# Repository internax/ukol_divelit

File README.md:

# SPI FLASH programátor
Tento repozitář obsahuje souboru k návrhu SPI Flash programátoru.

## Struktura
- Výrobní soubory jsou v adresáři: programator_spi/production/programator_spi.zip
- Schéma je dostupné v adresáři: programator_spi/schema_pdf/programator_spi.pdf
# Návrhová rozhodnutí

## Patice pro DIP8

Původní záměr byl použít ZIF socket, ten se však pro pDIP8 pouzdro prakticky nevyrábí. Zvolil jsem proto přesnou patici z doporučených komponent. Klíčovými kritérii byl nízký odpor kontaktů a zlaté pokovení pinů. Životnost patice je dle dokumentace přibližně 500 cyklů, což by pro daný účel mělo být dostatečné. Pokud by se požadavky na počet cyklů zvýšily, bylo by nutné přejít na ZIF patici většího formátu.

## USB rozhraní

Nejprve jsem navrhl USB rozhraní. Použil jsem ESD ochranu z doporučených komponent. Zvažoval jsem ještě ECMF02-2AMX6, která nabízí common mode ochranu a je použita například v referenčním designu MB1801.

Dále jsem přidal proudovou ochranu — polyfuse. Maximální proud jsem stanovil takto: flash paměť odebírá při zápisu až 30 mA, MCU pak dle datasheetu až 150 mA. Zvolil jsem proto polyfuse 200 mA, která poskytuje rozumnou rezervu; v případě potřeby ji lze snadno vyměnit.

Dle specifikace jsem na linku D+ přidal pull-up rezistor 1k5Ω.

## MCU

S STM32 jsem dosud nenavrhoval, proto jsem si stáhl AN a postupoval podle ní. Jako první jsem řešil napájení — přidal jsem blokovací kondenzátory na příslušné piny. Oddělení napájení analogové části jsem neřešil, protože zde nemá smysl.

Vybral jsem krystal 8 MHz tak, aby byl splněn margin, a navrhl jsem kondenzátory s tím, že Cp uvažuji jako 5 pF. Margin jsem ověřil dle AN2867 — vychází gm = 26,4 mA/V, rezerva je dostatečná.

## Programovací rozhraní

Pokračoval jsem programovacím rozhraním. Zvolil jsem SWD s výstupem SWO, konektor Tag-Connect.

## Tlačítka

Přidal jsem tlačítko RESET, protože je vhodné ho mít vždy vyvedené, a tlačítko BOOT pro změnu bootovacího režimu, například pro DFU přes USB. Tlačítko ERASE ani FLASH není zmíněno v zadání, takže jsem je nepřidával — zbytečná komplexita.

## Indikace

Pro indikaci stavu jsem zvolil adresovatelnou LED, která funguje s 5V logikou. Teoreticky by byl potřeba level shifter, nicméně v praxi funguje spolehlivě i bez něj, zejména na malých vzdálenostech.

## Flash

K napájení jsem přidal 100 nF kondenzátor, SPI jsem připojil k MCU, /WP a /HOLD jsem vyvedl na VDD, protože ani jednu z funkcí nepotřebuji. Na piny sdílené s MCU jsem přidal ESD ochranu.

## Test pady
Přidávám testpady s dírou uprostřed, protože v nich líp drží probe osciloskopu a ve dvouvrstvé desce ničemu nevadí.

*Text Návrhová rozhodnutí byl upravenu pomocí generativní umělé inteligence, originál je dostupný v: original_notes/notes.txt*

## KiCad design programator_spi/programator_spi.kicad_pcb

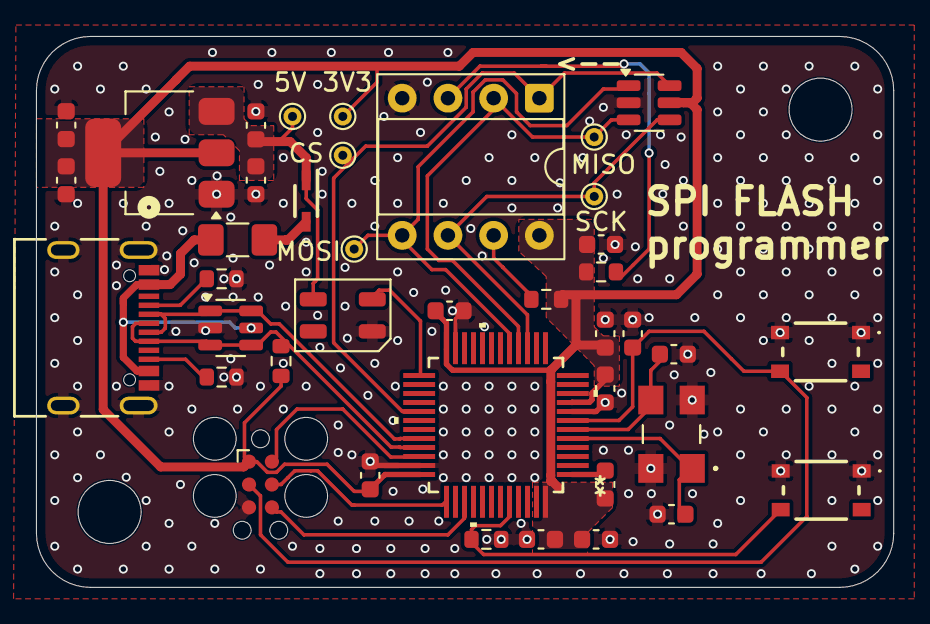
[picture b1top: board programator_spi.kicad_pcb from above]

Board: 2 copper layers, 47.6 x 30.6 mm, 42 parts (0 on the bottom side), 24 nets.

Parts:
3V3, 5V: TestPoint; TestPoint_THTPad_D1.0mm_Drill0.5mm
C1, C4, C5: 10u; C_0603_1608Metric
C2, C3, C6, C7, C8, C9, C11, C12, C15: 100n; C_0603_1608Metric
C10: 1u; C_0603_1608Metric
C13, C14: 27p; C_0603_1608Metric
CR1: LD1117S33CTR; SOT-223-3_TabPin2
CS: TestPoint; TestPoint_THTPad_D1.0mm_Drill0.5mm
D1: D_Schottky; SOD2512X110N
D2: WS2812B; LED_WS2812B-Mini_PLCC4_3.5x3.5mm
F1: Polyfuse; Fuse_1206_3216Metric_Pad1.42x1.75mm_HandSolder
H2, H3: MountingHole; MountingHole_3.5mm
IC1: SST25VF080B-50-4C-PAE; DIP-8_W7.62mm_Socket
J1: USB4105-GF-A; USB4105_GCT
J2: Conn_ARM_SWD_TagConnect_TC2030; Tag-Connect_TC2030-IDC-FP_2x03_P1.27mm_Vertical
MISO: TestPoint; TestPoint_THTPad_D1.0mm_Drill0.5mm
MOSI: TestPoint; TestPoint_THTPad_D1.0mm_Drill0.5mm
R1, R2: 5k1; R_0603_1608Metric
R3, R4, R5: 10k; R_0603_1608Metric
R7: 1k5; R_0603_1608Metric
S1, S2: TL3365AF180QG; TL3365AF250QG
SCK: TestPoint; TestPoint_THTPad_D1.0mm_Drill0.5mm
U1: STM32F103C8T6; LQFP48_STM-M
U2: USBLC6-4SC6; SOT-23-6
U3: USBLC6-2SC6; SOT-23-6
Y2: 8MHz; LFXTAL055663Reel

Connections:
+3.3V: 3V3.1, C3.2, C4.2, C5.2, C6.2, C7.2, C8.2, C9.1, C10.1, C11.2, C15.2, CR1.2 (VOUT), IC1.8 (VDD), J2.1 (VCC), R4.2, R5.2, R7.1, U1.9 (VDDA), U1.24 (VDD_1), U1.36 (VDD_2), U1.48 (VDD_3), U2.5 (VBUS)
+5V: 5V.1, C1.2, C2.2, CR1.3 (VIN), D1.1 (K), D2.1 (VDD)
/MCU - STM32F103/BOOT: R3.1, S2.4, U1.44 (BOOT0)
/MCU - STM32F103/NRST: C12.2, J2.3 (~RESET), S1.4, U1.7 (NRST)
/MCU - STM32F103/STATUS_LED: D2.4 (DIN), U1.25 (PB12)
/MCU - STM32F103/SWCLK: J2.4 (SWCLK), U1.37 (PA14)
/MCU - STM32F103/SWDIO: J2.2 (SWDIO), U1.34 (PA13)
/MCU - STM32F103/SWO: J2.6 (SWO), U1.39 (PB3)
/MCU - STM32F103/VBAT: C9.2, U1.1 (VBAT)
/SPI FLASH/CE#: CS.1, IC1.1 (CE#), U1.29 (PA8), U2.6 (I/O4)
/SPI FLASH/SCK: IC1.6 (SCK), SCK.1, U1.15 (PA5), U2.4 (I/O3)
/SPI FLASH/SI: IC1.5 (SI), MOSI.1, U1.17 (PA7), U2.1 (I/O1)
/SPI FLASH/SO: IC1.2 (SO), MISO.1, U1.16 (PA6), U2.3 (I/O2)
/USB-C/CC1: J1.A5 (CC1), R1.1
/USB-C/CC2: J1.B5 (CC2), R2.1
/USB-C/DN: J1.A7 (DN1), J1.B7 (DN2), U1.32 (PA11), U3.1 (I/O1), U3.6 (I/O1)
/USB-C/DP: J1.A6 (DP1), J1.B6 (DP2), R7.2, U1.33 (PA12), U3.3 (I/O2), U3.4 (I/O2)
/USB-C/Vbus: F1.2, J1.A4-B9 (VBUS), J1.B4-A9 (VBUS), U3.5 (VBUS)
GND: C1.1, C2.1, C3.1, C4.1, C5.1, C6.1, C7.1, C8.1, C10.2, C11.1, C12.1, C13.2, C14.2, C15.1, CR1.1 (ADJ/GND), D2.3 (VSS), IC1.4 (VSS), J1.A1-B12 (GND), J1.B1-A12 (GND), J2.5 (GND), R1.2, R2.2, R3.2, S1.1, S1.2, S2.1, S2.2, U1.8 (VSSA), U1.23 (VSS_1), U1.35 (VSS_2), U1.47 (VSS_3), U2.2 (GND), U3.2 (GND), Y2.2, Y2.4
unnamed: D1.2 (A), F1.1
unnamed: IC1.7 (HOLD#), R5.1
unnamed: IC1.3 (WP#), R4.1
unnamed: C14.1, U1.5 (OSC_IN), Y2.1
unnamed: C13.1, U1.6 (OSC_OUT), Y2.3

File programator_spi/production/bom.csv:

Designator,Footprint,Quantity,Value,LCSC Part #
"3V3, 5V, CS, MISO, MOSI, SCK",TestPoint_THTPad_D1.0mm_Drill0.5mm,6,TestPoint,
"C1, C4, C5",0603,3,10u,
C10,0603,1,1u,
"C11, C12, C15, C2, C3, C6, C7, C8, C9",0603,9,100n,
"C13, C14",0603,2,27p,
CR1,SOT-223-3_TabPin2,1,LD1117S33CTR,
D1,SOD2512X110N,1,D_Schottky,
D2,LED_WS2812B-Mini_PLCC4_3.5x3.5mm,1,WS2812B,
F1,1206,1,Polyfuse,
"H2, H3",MountingHole_3.5mm,2,MountingHole,
IC1,DIP-8_W7.62mm_Socket,1,SST25VF080B-50-4C-PAE,
J1,USB4105_GCT,1,USB4105-GF-A,
"R1, R2",0603,2,5k1,
"R3, R4, R5",0603,3,10k,
R7,0603,1,1k5,
"S1, S2",TL3365AF250QG,2,TL3365AF180QG,
U1,LQFP48_STM-M,1,STM32F103C8T6,
U2,SOT-23-6,1,USBLC6-4SC6,
U3,SOT-23-6,1,USBLC6-2SC6,
Y2,LFXTAL055663Reel,1,8MHz,

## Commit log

2026-05-01 spi_flash_v1.0
2026-05-01 name change
2026-05-01 Add README.md for SPI Flash programmer project
    Added detailed documentation for the SPI Flash programmer, including design decisions, structure, and components used.
2026-05-01 Add test pads to README for oscilloscope probes
    Added test pads with a hole in the center for better probe hold.
2026-05-01 notes
